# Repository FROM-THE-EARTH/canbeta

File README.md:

# canbeta

東北大学 [FTE](https://www.fte-tohoku.org/) CanSat チーム9期代のプロジェクトです．

## Dependancies

[Pipfile](./Pipfile) を参照してください．
フレームワークは [pisat](https://github.com/jjj999/pisat) を使っています．

## 開発者へ

* 必ずクローンしたら pipenv で Pipfile に沿った仮想環境を作成してください

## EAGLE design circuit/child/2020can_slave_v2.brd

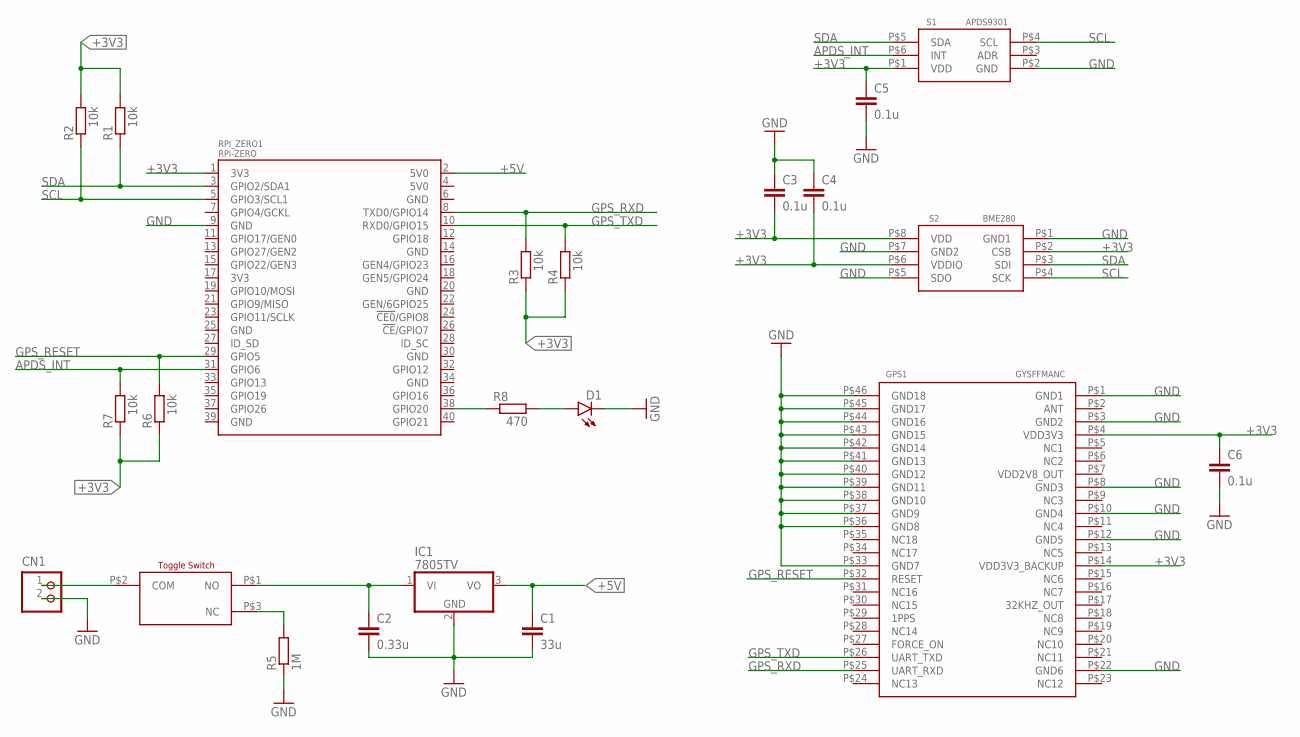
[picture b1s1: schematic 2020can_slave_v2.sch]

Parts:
C1: 33u; C5B3
C2: 0.33u; C5B3
C3, C4, C5, C6: 0.1u; C1206
CN1: B2P-VH
D1: SFH482
GPS1: GYSFFMANC
IC1: 7805TV; TO220V
R1, R2, R3, R4, R6, R7: 10k; R1206
R5: 1M; 0207/10
R8: 470; 0207/10
RPI_ZERO1: RPI-ZERO; RASP_PI_ZERO_BOARD_FULL
S1: APDS9301
S2: BME280
SWITCH_2MS1T2B4M2QES1: SWITCH_2MS1T2B4M2QES

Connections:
+3V3: C3.2, C4.2, C5.1, C6.1, GPS1.P$4 (VDD3V3), GPS1.P$14 (VDD3V3_BACKUP), R1.2, R2.2, R3.1, R4.1, R6.1, R7.1, RPI_ZERO1.1 (3V3), S1.P$1 (VDD), S2.P$2 (CSB), S2.P$6 (VDDIO), S2.P$8 (VDD)
+5V: C1.1, IC1.3 (VO), RPI_ZERO1.2 (5V0)
APDS_INT: R7.2, RPI_ZERO1.31 (GPIO6), S1.P$6 (INT)
GND: C1.2, C2.2, C3.1, C4.1, C5.2, C6.2, CN1.2, D1.K (C), GPS1.P$1 (GND1), GPS1.P$3 (GND2), GPS1.P$8 (GND3), GPS1.P$10 (GND4), GPS1.P$12 (GND5), GPS1.P$22 (GND6), GPS1.P$33 (GND7), GPS1.P$36 (GND8), GPS1.P$37 (GND9), GPS1.P$38 (GND10), GPS1.P$39 (GND11), GPS1.P$40 (GND12), GPS1.P$41 (GND13), GPS1.P$42 (GND14), GPS1.P$43 (GND15), GPS1.P$44 (GND16), GPS1.P$45 (GND17), GPS1.P$46 (GND18), IC1.2 (GND), R5.1, RPI_ZERO1.9 (GND), S1.P$2 (GND), S2.P$1 (GND1), S2.P$5 (SDO), S2.P$7 (GND2)
GPS_RESET: GPS1.P$32 (RESET), R6.2, RPI_ZERO1.29 (GPIO5)
GPS_RXD: GPS1.P$25 (UART_RXD), R3.2, RPI_ZERO1.8 (TXD0/GPIO14)
GPS_TXD: GPS1.P$26 (UART_TXD), R4.2, RPI_ZERO1.10 (RXD0/GPIO15)
unnamed: R8.1, RPI_ZERO1.38 (GPIO20)
unnamed: D1.A, R8.2
unnamed: R5.2, SWITCH_2MS1T2B4M2QES1.P$3 (NC)
SCL: R2.1, RPI_ZERO1.5 (GPIO3/SCL1), S1.P$4 (SCL), S2.P$4 (SCK)
SDA: R1.1, RPI_ZERO1.3 (GPIO2/SDA1), S1.P$5 (SDA), S2.P$3 (SDI)
V+: CN1.1, SWITCH_2MS1T2B4M2QES1.P$2 (COM)
VIN: C2.1, IC1.1 (VI), SWITCH_2MS1T2B4M2QES1.P$1 (NO)

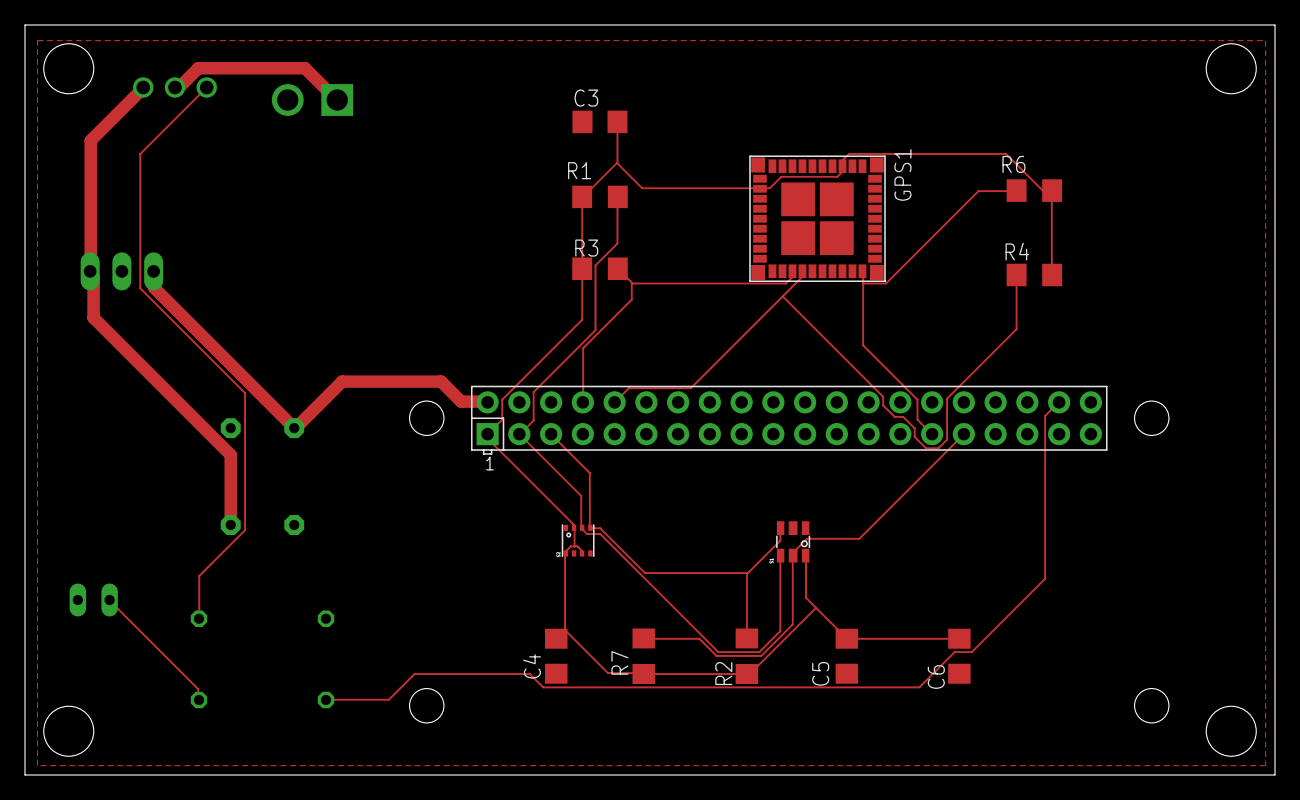
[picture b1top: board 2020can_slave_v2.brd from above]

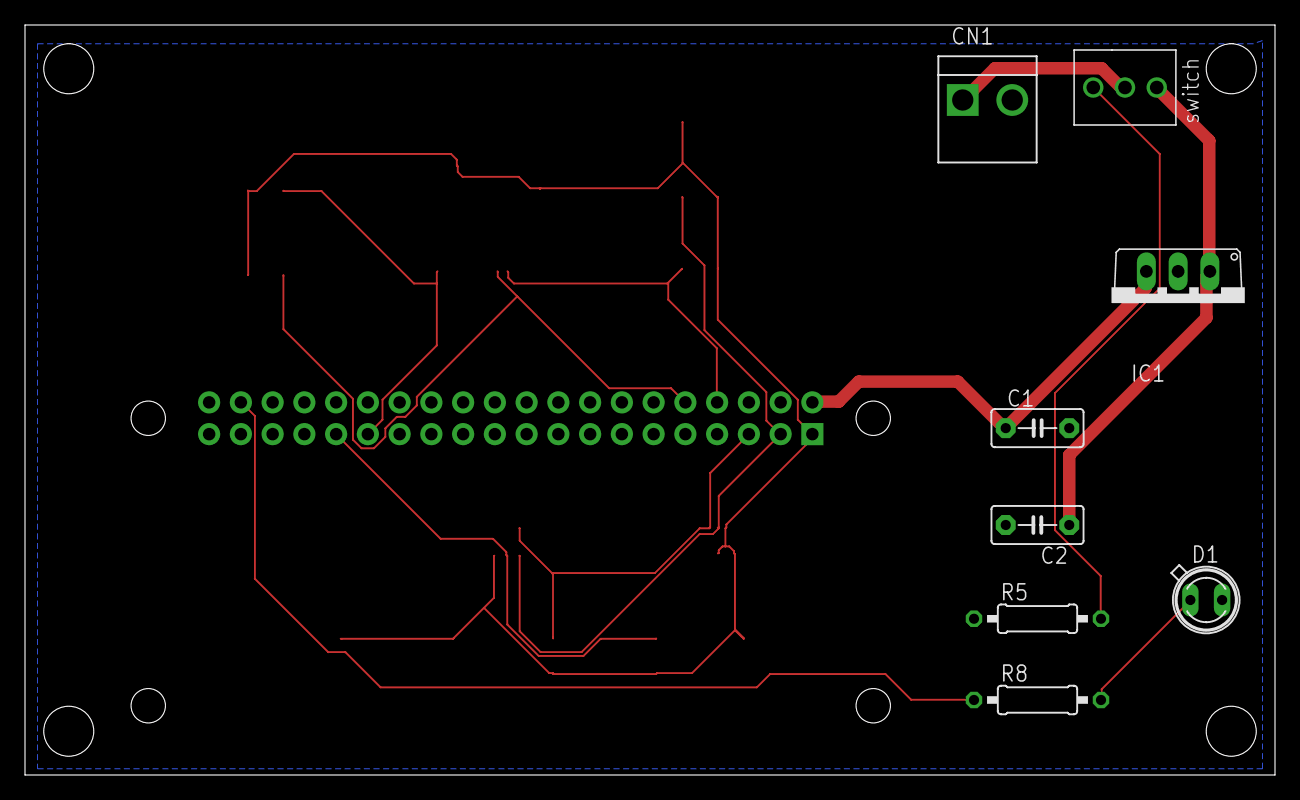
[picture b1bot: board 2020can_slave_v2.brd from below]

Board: 2 copper layers, 100.0 x 60.0 mm, 22 parts (8 on the bottom side), 14 nets.

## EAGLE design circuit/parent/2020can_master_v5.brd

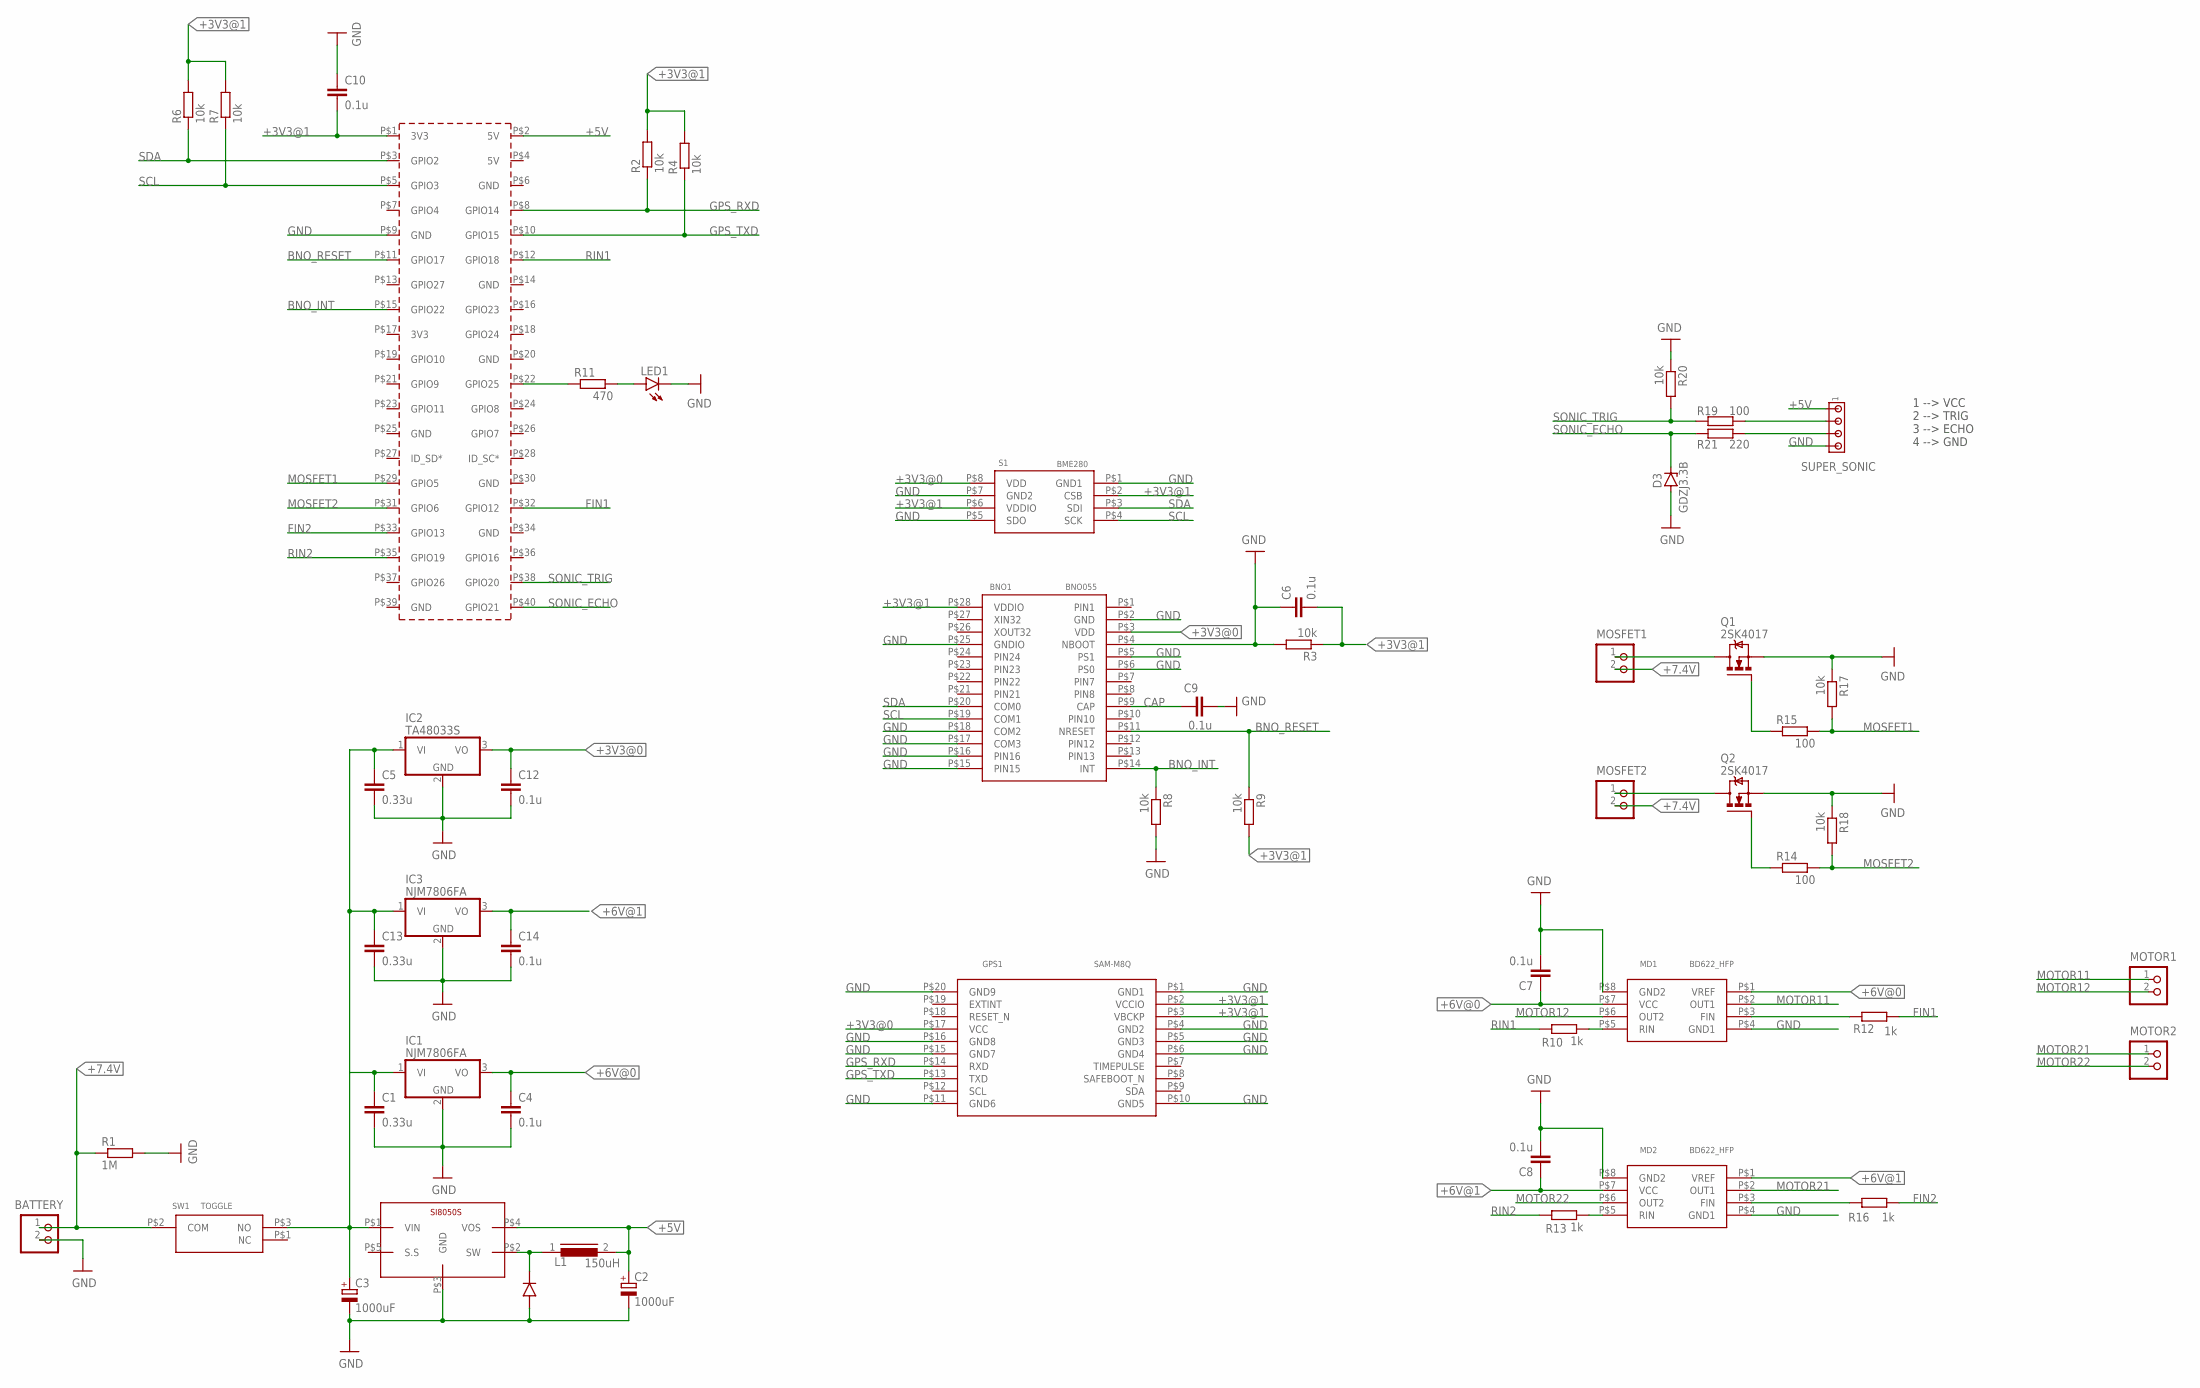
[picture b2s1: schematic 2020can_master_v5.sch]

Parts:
BATTERY: B2P-VH
BNO1: BNO055
C1, C5, C13: 0.33u; C5B3
C2, C3: 1000uF; E5-10,5
C4, C12, C14: 0.1u; C5B3
C6, C7, C8, C9, C10: 0.1u; C1206
D3: GDZJ3.3B; DO35Z10
DIODE_1.1: DIODE_1.5
GPS1: SAM-M8Q
IC1, IC3: NJM7806FA; TO220V
IC2: TA48033S; TO220V
L1: 150uH; SFT830D
LED1: LED5MM
MD1, MD2: BD622_HFP; BD62**_HRP7
MOSFET1, MOSFET2: B2P-VH
MOTOR1, MOTOR2: B2P-VH
PCB1: RPI3RPI3; RPI3
Q1, Q2: 2SK4017; TO220BV
R1: 1M; R2012
R2, R3, R4, R6, R7, R8, R9, R17, R18, R20: 10k; R2012
R10, R12, R13, R16: 1k; R2012
R11: 470; 0207/10
R14, R15, R19: 100; 0207/10
R21: 220; 0207/10
S1: BME280
SI8050S1: SI8050S
SUPER_SONIC: MTA04-100; 10X04MTA
SW1: TOGGLE; TOGGLE_1MS1-T1-B1-M2-Q-N-S

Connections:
+3V3@0: BNO1.P$3 (VDD), C12.1, GPS1.P$17 (VCC), IC2.3 (VO), S1.P$8 (VDD)
+3V3@1: BNO1.P$28 (VDDIO), C6.2, C10.2, GPS1.P$2 (VCCIO), GPS1.P$3 (VBCKP), PCB1.P$1 (3V3), R2.2, R3.1, R4.2, R6.2, R7.2, R9.2, S1.P$2 (CSB), S1.P$6 (VDDIO)
+5V: C2.+, L1.2, PCB1.P$2 (5V), SI8050S1.P$4 (VOS), SUPER_SONIC.1
+6V@0: C4.1, C7.1, IC1.3 (VO), MD1.P$1 (VREF), MD1.P$7 (VCC)
+6V@1: C8.1, C14.1, IC3.3 (VO), MD2.P$1 (VREF), MD2.P$7 (VCC)
+7.4V: BATTERY.1, MOSFET1.2, MOSFET2.2, R1.1, SW1.P$2 (COM)
BNO_INT: BNO1.P$14 (INT), PCB1.P$15 (GPIO22), R8.1
BNO_RESET: BNO1.P$11 (NRESET), PCB1.P$11 (GPIO17), R9.1
CAP: BNO1.P$9 (CAP), C9.1
FIN1: PCB1.P$32 (GPIO12), R12.2
FIN2: PCB1.P$33 (GPIO13), R16.2
GND: BATTERY.2, BNO1.P$2 (GND), BNO1.P$4 (NBOOT), BNO1.P$5 (PS1), BNO1.P$6 (PS0), BNO1.P$15 (PIN15), BNO1.P$16 (PIN16), BNO1.P$17 (COM3), BNO1.P$18 (COM2), BNO1.P$25 (GNDIO), C1.2, C2.-, C3.-, C4.2, C5.2, C6.1, C7.2, C8.2, C9.2, C10.1, C12.2, D3.A, DIODE_1.1.P$1 (ANODE), GPS1.P$1 (GND1), GPS1.P$4 (GND2), GPS1.P$5 (GND3), GPS1.P$6 (GND4), GPS1.P$10 (GND5), GPS1.P$11 (GND6), GPS1.P$15 (GND7), GPS1.P$16 (GND8), GPS1.P$20 (GND9), IC1.2 (GND), IC2.2 (GND), LED1.K (C), MD1.P$4 (GND1), MD1.P$8 (GND2), MD2.P$4 (GND1), MD2.P$8 (GND2), PCB1.P$9 (GND), Q1.S, Q2.S, R1.2, R3.2, R8.2, R17.1, R18.1, R20.1, S1.P$1 (GND1), S1.P$5 (SDO), S1.P$7 (GND2), SI8050S1.P$3 (GND), SUPER_SONIC.4
GPS_RXD: GPS1.P$14 (RXD), PCB1.P$8 (GPIO14), R2.1
GPS_TXD: GPS1.P$13 (TXD), PCB1.P$10 (GPIO15), R4.1
MOSFET1: PCB1.P$29 (GPIO5), R15.2, R17.2
MOSFET2: PCB1.P$31 (GPIO6), R14.2, R18.2
MOTOR11: MD1.P$2 (OUT1), MOTOR1.1
MOTOR12: MD1.P$6 (OUT2), MOTOR1.2
MOTOR21: MD2.P$2 (OUT1), MOTOR2.1
MOTOR22: MD2.P$6 (OUT2), MOTOR2.2
unnamed: DIODE_1.1.P$2 (CATHODE), L1.1, SI8050S1.P$2 (SW)
unnamed: PCB1.P$22 (GPIO25), R11.1
unnamed: C1.1, C3.+, C5.1, C13.1, IC1.1 (VI), IC2.1 (VI), IC3.1 (VI), SI8050S1.P$1 (VIN), SW1.P$3 (NO)
unnamed: LED1.A, R11.2
unnamed: MOSFET1.1, Q1.D
unnamed: MD1.P$3 (FIN), R12.1
unnamed: MOSFET2.1, Q2.D
unnamed: MD1.P$5 (RIN), R10.2
unnamed: Q1.G, R15.1
unnamed: Q2.G, R14.1
unnamed: MD2.P$3 (FIN), R16.1
unnamed: C13.2, C14.2, IC3.2 (GND)
unnamed: MD2.P$5 (RIN), R13.2
unnamed: R19.2, SUPER_SONIC.2
unnamed: R21.2, SUPER_SONIC.3
RIN1: PCB1.P$12 (GPIO18), R10.1
RIN2: PCB1.P$35 (GPIO19), R13.1
SCL: BNO1.P$19 (COM1), PCB1.P$5 (GPIO3), R7.1, S1.P$4 (SCK)
SDA: BNO1.P$20 (COM0), PCB1.P$3 (GPIO2), R6.1, S1.P$3 (SDI)
SONIC_ECHO: D3.C, PCB1.P$40 (GPIO21), R21.1
SONIC_TRIG: PCB1.P$38 (GPIO20), R19.1, R20.2

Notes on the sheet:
1 --> VCC 2 --> TRIG 3 --> ECHO 4 --> GND

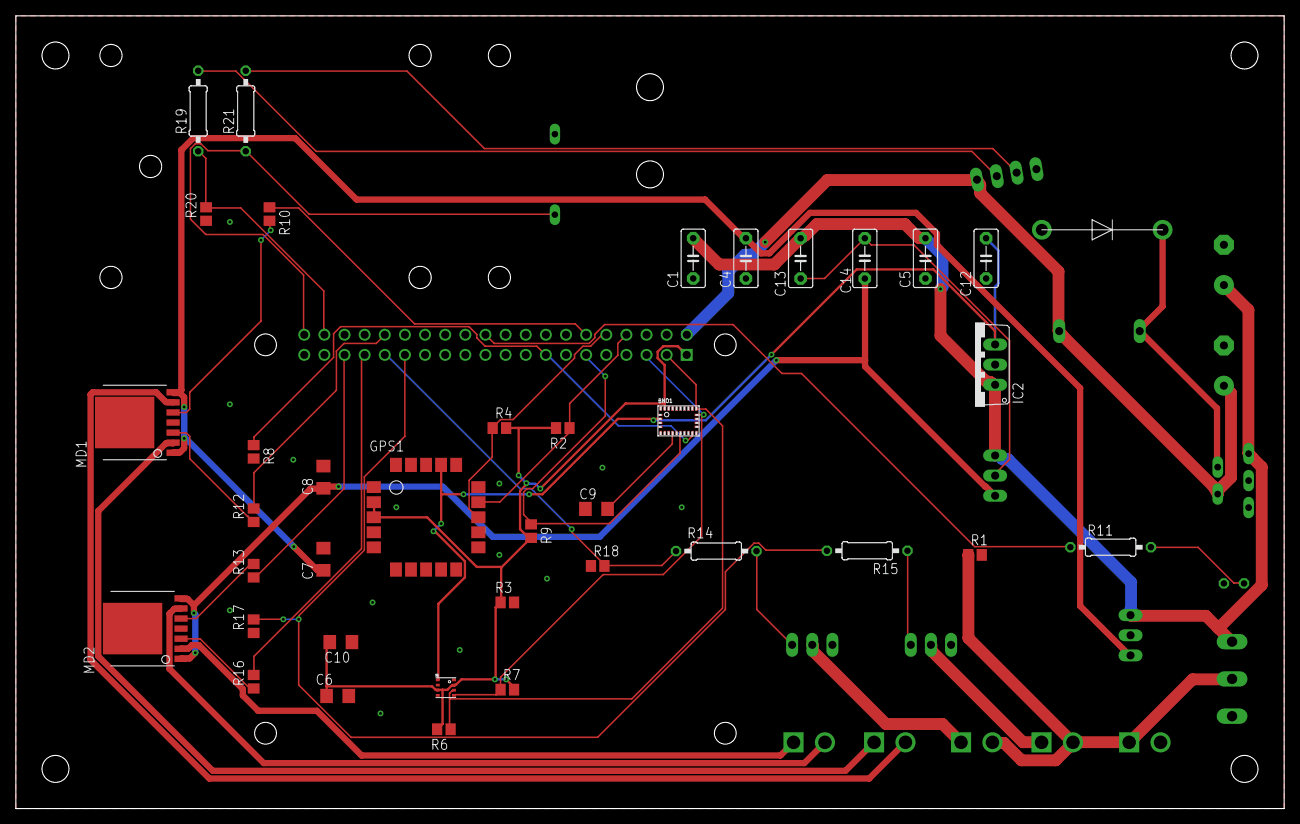
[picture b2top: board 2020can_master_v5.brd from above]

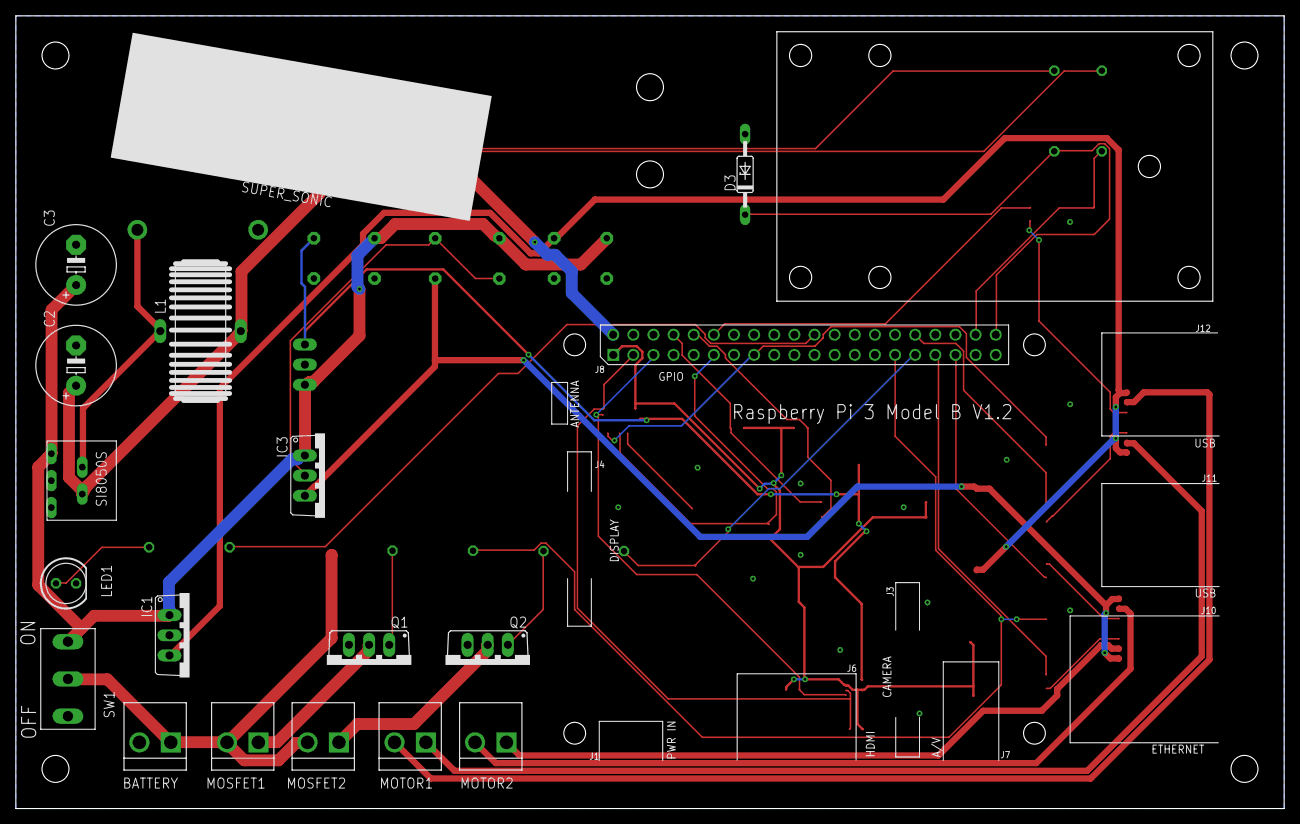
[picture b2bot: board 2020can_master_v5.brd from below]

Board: 2 copper layers, 160.0 x 100.0 mm, 56 parts (18 on the bottom side), 41 nets.

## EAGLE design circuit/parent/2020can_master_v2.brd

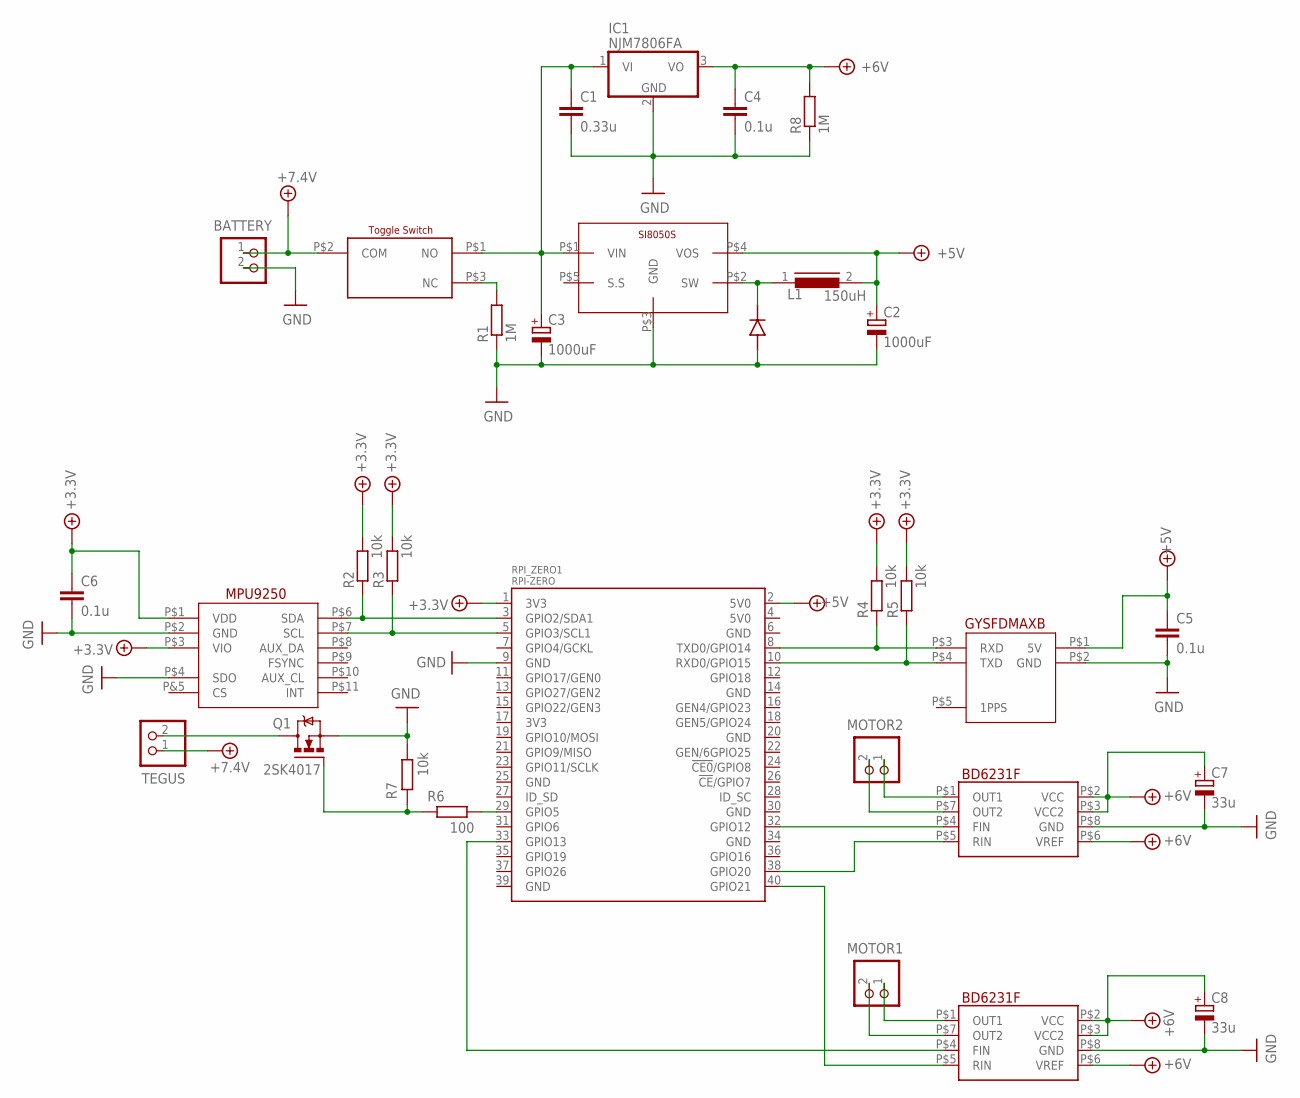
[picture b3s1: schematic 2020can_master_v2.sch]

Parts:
BATTERY: B2P-VH
BD6231F1, BD6231F2: BD6231F; BD62**_SOP8
C1: 0.33u; C5B3
C2, C3: 1000uF; E5-10,5
C4, C5, C6: 0.1u; C5B3
C7, C8: 33u; E2,5-6E
DIODE_1.1: DIODE_1.5
GYSFDMAXB1: GYSFDMAXB
IC1: NJM7806FA; TO220V
L1: 150uH; SFT830D
MOTOR1, MOTOR2: B2P-VH
MPU1: MPU9250
Q1: 2SK4017; TO220BV
R1, R8: 1M; 0207/10
R2, R3, R4, R5, R7: 10k; 0207/10
R6: 100; 0207/10
RPI_ZERO1: RPI-ZERO; RASP_PI_ZERO_BOARD_FULL
SI8050S1: SI8050S
SWITCH_2MS1T2B4M2QES1: SWITCH_2MS1T2B4M2QES
TEGUS: B2P-VH

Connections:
+4.1V: MPU1.P$3 (VIO), R2.2, R3.2, R4.2, R5.2, RPI_ZERO1.1 (3V3)
+5V: C2.+, C5.1, GYSFDMAXB1.P$1 (5V), L1.2, RPI_ZERO1.2 (5V0), SI8050S1.P$4 (VOS)
+7V: BD6231F1.P$2 (VCC), BD6231F1.P$3 (VCC2), BD6231F1.P$6 (VREF), BD6231F2.P$2 (VCC), BD6231F2.P$3 (VCC2), BD6231F2.P$6 (VREF), C4.1, C7.+, C8.+, IC1.3 (VO), R8.2
+8V: BATTERY.1, SWITCH_2MS1T2B4M2QES1.P$2 (COM), TEGUS.1
GND: BATTERY.2, BD6231F1.P$8 (GND), BD6231F2.P$8 (GND), C1.2, C2.-, C3.-, C4.2, C5.2, C6.2, C7.-, C8.-, DIODE_1.1.P$1 (ANODE), GYSFDMAXB1.P$2 (GND), IC1.2 (GND), MPU1.P$2 (GND), MPU1.P$4 (SDO), Q1.S, R1.1, R7.1, R8.1, RPI_ZERO1.9 (GND), SI8050S1.P$3 (GND)
MOS_+: Q1.D, TEGUS.2
unnamed: R1.2, SWITCH_2MS1T2B4M2QES1.P$3 (NC)
unnamed: DIODE_1.1.P$2 (CATHODE), L1.1, SI8050S1.P$2 (SW)
unnamed: MPU1.P$6 (SDA), R2.1, RPI_ZERO1.3 (GPIO2/SDA1)
unnamed: C1.1, C3.+, IC1.1 (VI), SI8050S1.P$1 (VIN), SWITCH_2MS1T2B4M2QES1.P$1 (NO)
unnamed: BD6231F1.P$4 (FIN), RPI_ZERO1.32 (GPIO12)
unnamed: MPU1.P$7 (SCL), R3.1, RPI_ZERO1.5 (GPIO3/SCL1)
unnamed: GYSFDMAXB1.P$3 (RXD), R4.1, RPI_ZERO1.8 (TXD0/GPIO14)
unnamed: GYSFDMAXB1.P$4 (TXD), R5.1, RPI_ZERO1.10 (RXD0/GPIO15)
unnamed: BD6231F1.P$1 (OUT1), MOTOR2.1
unnamed: BD6231F2.P$4 (FIN), RPI_ZERO1.33 (GPIO13)
unnamed: BD6231F1.P$7 (OUT2), MOTOR2.2
unnamed: BD6231F1.P$5 (RIN), RPI_ZERO1.38 (GPIO20)
unnamed: BD6231F2.P$1 (OUT1), MOTOR1.1
unnamed: BD6231F2.P$7 (OUT2), MOTOR1.2
unnamed: BD6231F2.P$5 (RIN), RPI_ZERO1.40 (GPIO21)
unnamed: Q1.G, R6.2, R7.2
unnamed: R6.1, RPI_ZERO1.29 (GPIO5)
unnamed: C6.1, MPU1.P$1 (VDD)

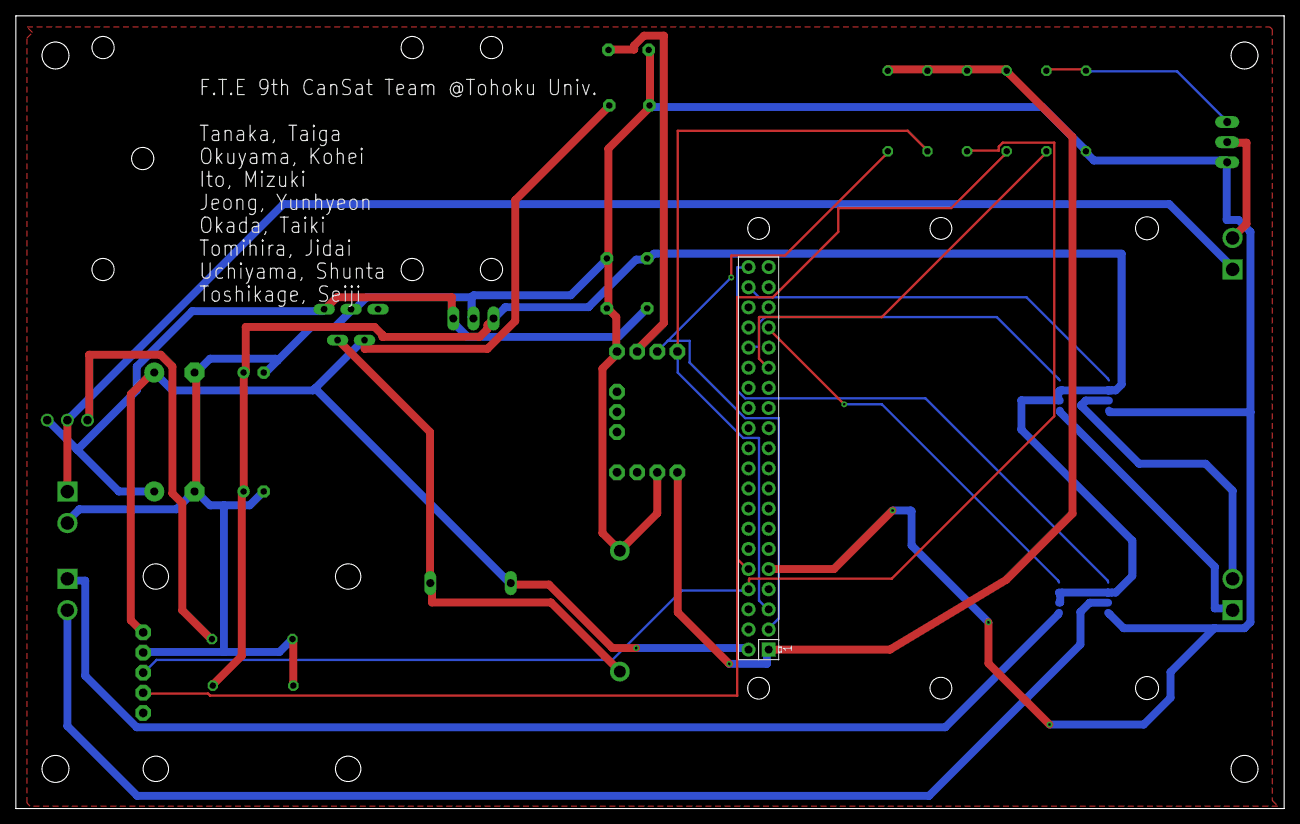
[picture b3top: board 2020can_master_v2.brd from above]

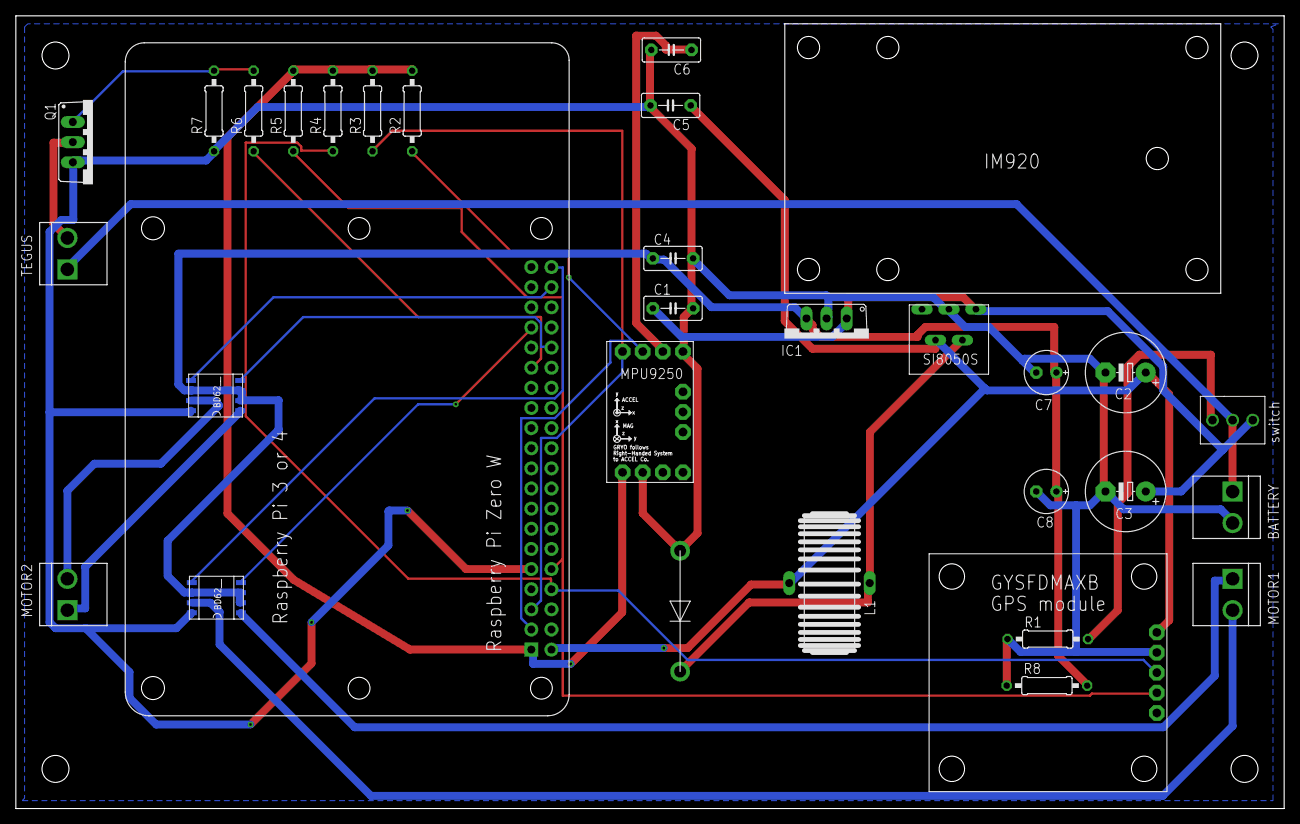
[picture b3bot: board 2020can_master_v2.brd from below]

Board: 2 copper layers, 160.0 x 100.0 mm, 31 parts (30 on the bottom side), 24 nets.

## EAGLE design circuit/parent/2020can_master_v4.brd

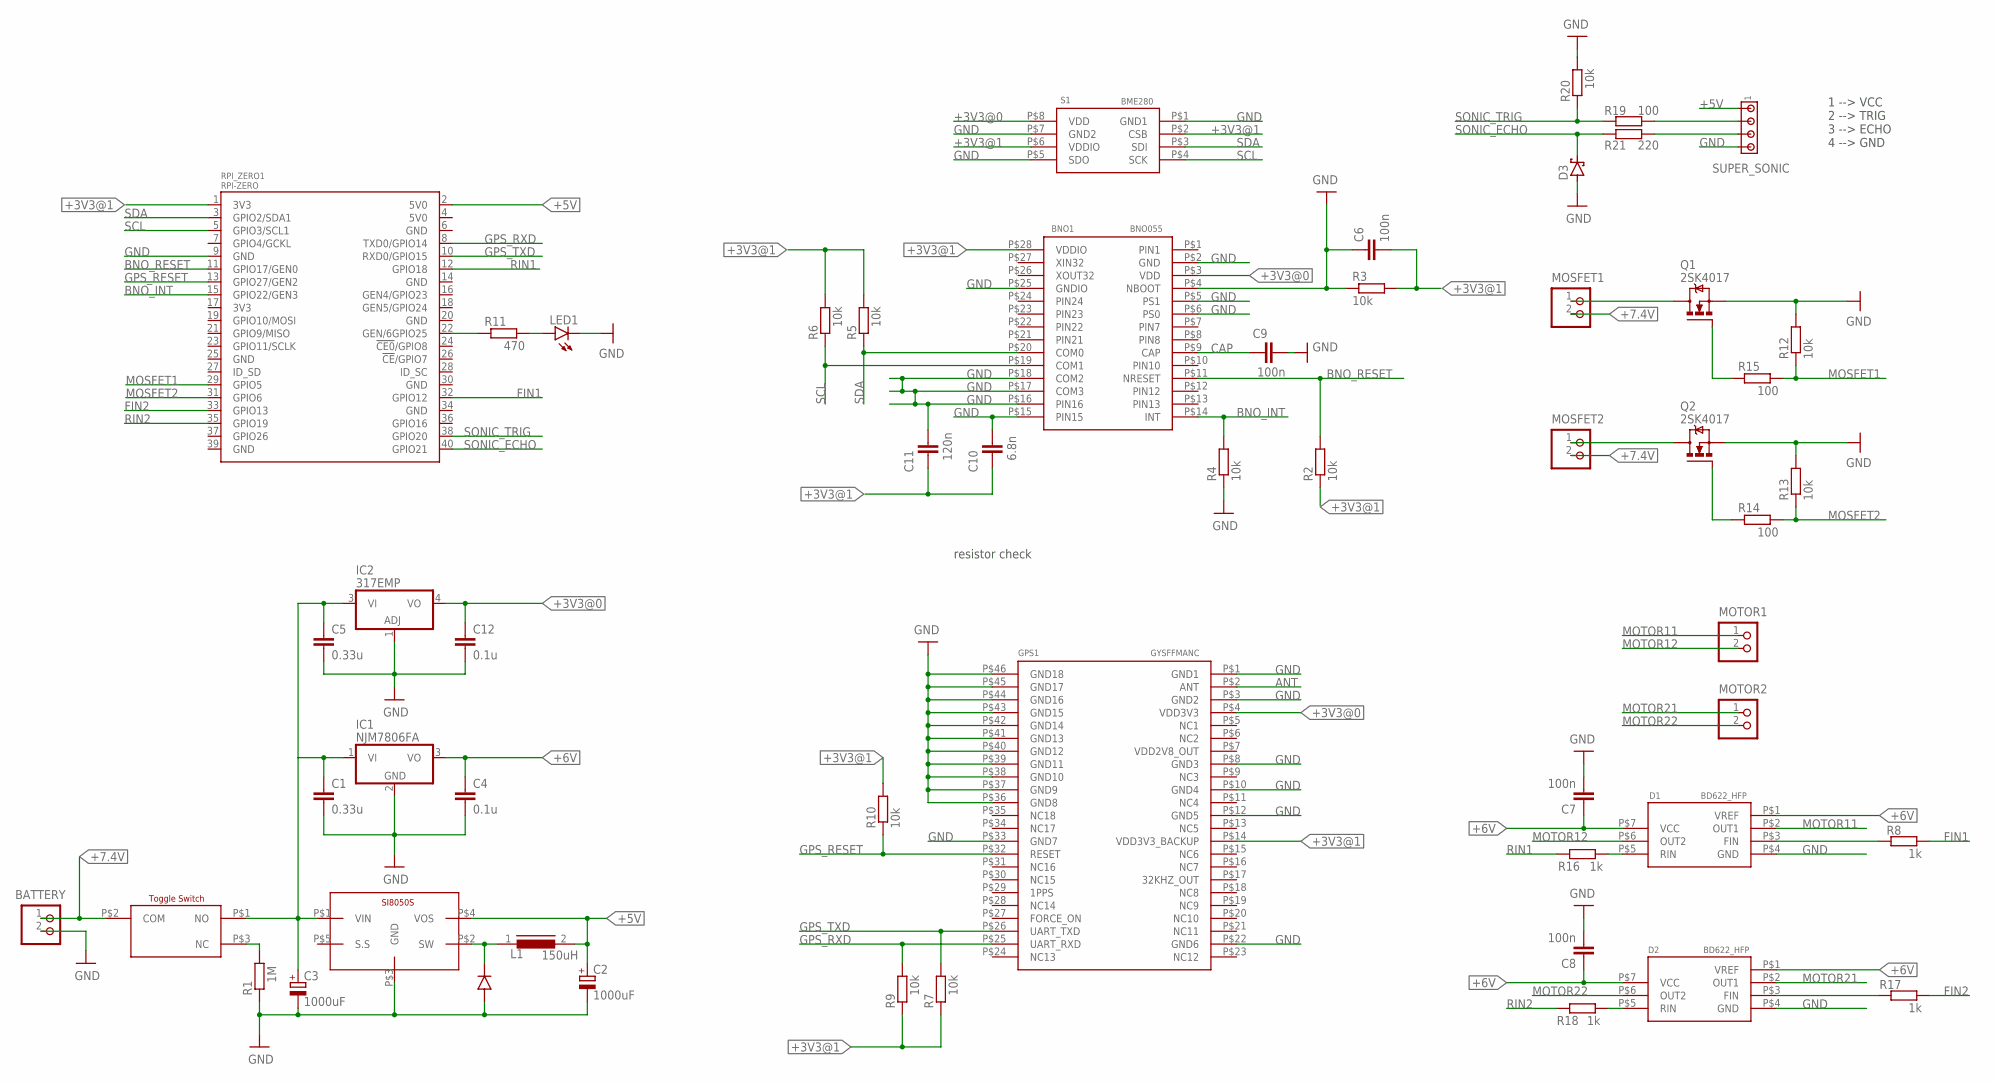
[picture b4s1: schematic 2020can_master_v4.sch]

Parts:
BATTERY: B2P-VH
BNO1: BNO055
C1, C5: 0.33u; C5B3
C2, C3: 1000uF; E5-10,5
C4, C12: 0.1u; C5B3
C6, C7, C8, C9: 100n; C1206
C10: 6.8n; C1206
C11: 120n; C1206
D1, D2: BD622_HFP; BD62**_HRP7
D3: 15KEXXD; DO201T15
DIODE_1.1: DIODE_1.5
GPS1: GYSFFMANC
IC1: NJM7806FA; TO220V
IC2: 317EMP; SOT223
L1: 150uH; SFT830D
LED1: LED5MM
MOSFET1, MOSFET2: B2P-VH
MOTOR1, MOTOR2: B2P-VH
Q1, Q2: 2SK4017; TO220BV
R1: 1M; R1206
R2, R3, R4, R5, R6, R7, R9, R10, R12, R13, R20: 10k; R1206
R8, R16, R17, R18: 1k; R1206
R11: 470; 0207/10
R14, R15, R19: 100; 0207/10
R21: 220; 0207/10
RPI_ZERO1: RPI-ZERO; RASP_PI_ZERO_BOARD_FULL
S1: BME280
SI8050S1: SI8050S
SUPER_SONIC: MTA04-100; 10X04MTA
SWITCH_2MS1T2B4M2QES1: SWITCH_2MS1T2B4M2QES

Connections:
+3V3@0: BNO1.P$3 (VDD), C12.1, GPS1.P$4 (VDD3V3), IC2.4 (VO), S1.P$8 (VDD)
+3V3@1: BNO1.P$28 (VDDIO), C6.2, C10.1, C11.1, GPS1.P$14 (VDD3V3_BACKUP), R2.1, R3.2, R5.2, R6.2, R7.1, R9.1, R10.2, RPI_ZERO1.1 (3V3), S1.P$2 (CSB), S1.P$6 (VDDIO)
+5V: C2.+, L1.2, RPI_ZERO1.2 (5V0), SI8050S1.P$4 (VOS), SUPER_SONIC.1
+6V: C4.1, C7.1, C8.1, D1.P$1 (VREF), D1.P$7 (VCC), D2.P$1 (VREF), D2.P$7 (VCC), IC1.3 (VO)
+7.4V: BATTERY.1, MOSFET1.2, MOSFET2.2, SWITCH_2MS1T2B4M2QES1.P$2 (COM)
ANT: GPS1.P$2 (ANT)
BNO_INT: BNO1.P$14 (INT), R4.2, RPI_ZERO1.15 (GPIO22/GEN3)
BNO_RESET: BNO1.P$11 (NRESET), R2.2, RPI_ZERO1.11 (GPIO17/GEN0)
CAP: BNO1.P$9 (CAP), C9.1
FIN1: R8.1, RPI_ZERO1.32 (GPIO12)
FIN2: R17.1, RPI_ZERO1.33 (GPIO13)
GND: BATTERY.2, BNO1.P$2 (GND), BNO1.P$4 (NBOOT), BNO1.P$5 (PS1), BNO1.P$6 (PS0), BNO1.P$15 (PIN15), BNO1.P$16 (PIN16), BNO1.P$17 (COM3), BNO1.P$18 (COM2), BNO1.P$25 (GNDIO), C1.2, C2.-, C3.-, C4.2, C5.2, C6.1, C7.2, C8.2, C9.2, C10.2, C11.2, C12.2, D1.P$4 (GND), D2.P$4 (GND), D3.A, DIODE_1.1.P$1 (ANODE), GPS1.P$1 (GND1), GPS1.P$3 (GND2), GPS1.P$8 (GND3), GPS1.P$10 (GND4), GPS1.P$12 (GND5), GPS1.P$22 (GND6), GPS1.P$33 (GND7), GPS1.P$36 (GND8), GPS1.P$37 (GND9), GPS1.P$38 (GND10), GPS1.P$39 (GND11), GPS1.P$40 (GND12), GPS1.P$41 (GND13), GPS1.P$42 (GND14), GPS1.P$43 (GND15), GPS1.P$44 (GND16), GPS1.P$45 (GND17), GPS1.P$46 (GND18), IC1.2 (GND), IC2.1 (ADJ), LED1.K (C), Q1.S, Q2.S, R1.1, R3.1, R4.1, R12.2, R13.2, R20.2, RPI_ZERO1.9 (GND), S1.P$1 (GND1), S1.P$5 (SDO), S1.P$7 (GND2), SI8050S1.P$3 (GND), SUPER_SONIC.4
GPS_RESET: GPS1.P$32 (RESET), R10.1, RPI_ZERO1.13 (GPIO27/GEN2)
GPS_RXD: GPS1.P$25 (UART_RXD), R9.2, RPI_ZERO1.8 (TXD0/GPIO14)
GPS_TXD: GPS1.P$26 (UART_TXD), R7.2, RPI_ZERO1.10 (RXD0/GPIO15)
MOSFET1: R12.1, R15.2, RPI_ZERO1.29 (GPIO5)
MOSFET2: R13.1, R14.2, RPI_ZERO1.31 (GPIO6)
MOTOR11: D1.P$2 (OUT1), MOTOR1.1
MOTOR12: D1.P$6 (OUT2), MOTOR1.2
MOTOR21: D2.P$2 (OUT1), MOTOR2.1
MOTOR22: D2.P$6 (OUT2), MOTOR2.2
unnamed: R1.2, SWITCH_2MS1T2B4M2QES1.P$3 (NC)
unnamed: DIODE_1.1.P$2 (CATHODE), L1.1, SI8050S1.P$2 (SW)
unnamed: R11.1, RPI_ZERO1.22 (GEN/6GPIO25)
unnamed: C1.1, C3.+, C5.1, IC1.1 (VI), IC2.3 (VI), SI8050S1.P$1 (VIN), SWITCH_2MS1T2B4M2QES1.P$1 (NO)
unnamed: LED1.A, R11.2
unnamed: MOSFET1.1, Q1.D
unnamed: D1.P$3 (FIN), R8.2
unnamed: MOSFET2.1, Q2.D
unnamed: D1.P$5 (RIN), R16.1
unnamed: Q1.G, R15.1
unnamed: Q2.G, R14.1
unnamed: D2.P$3 (FIN), R17.2
unnamed: D2.P$5 (RIN), R18.1
unnamed: R19.2, SUPER_SONIC.2
unnamed: R21.2, SUPER_SONIC.3
RIN1: R16.2, RPI_ZERO1.12 (GPIO18)
RIN2: R18.2, RPI_ZERO1.35 (GPIO19)
SCL: BNO1.P$19 (COM1), R6.1, RPI_ZERO1.5 (GPIO3/SCL1), S1.P$4 (SCK)
SDA: BNO1.P$20 (COM0), R5.1, RPI_ZERO1.3 (GPIO2/SDA1), S1.P$3 (SDI)
SONIC_ECHO: D3.C, R21.1, RPI_ZERO1.40 (GPIO21)
SONIC_TRIG: R19.1, R20.1, RPI_ZERO1.38 (GPIO20)

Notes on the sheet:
resistor check
1 --> VCC 2 --> TRIG 3 --> ECHO 4 --> GND

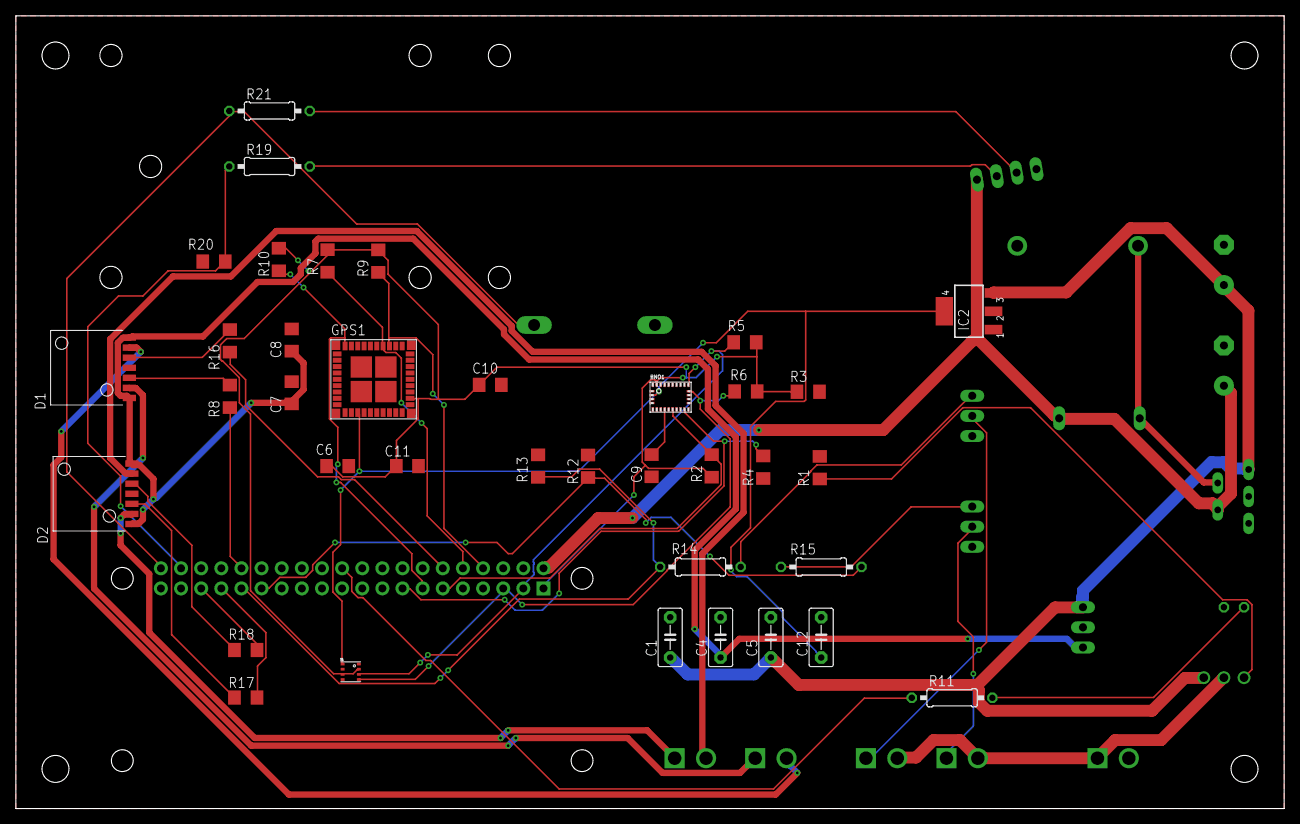
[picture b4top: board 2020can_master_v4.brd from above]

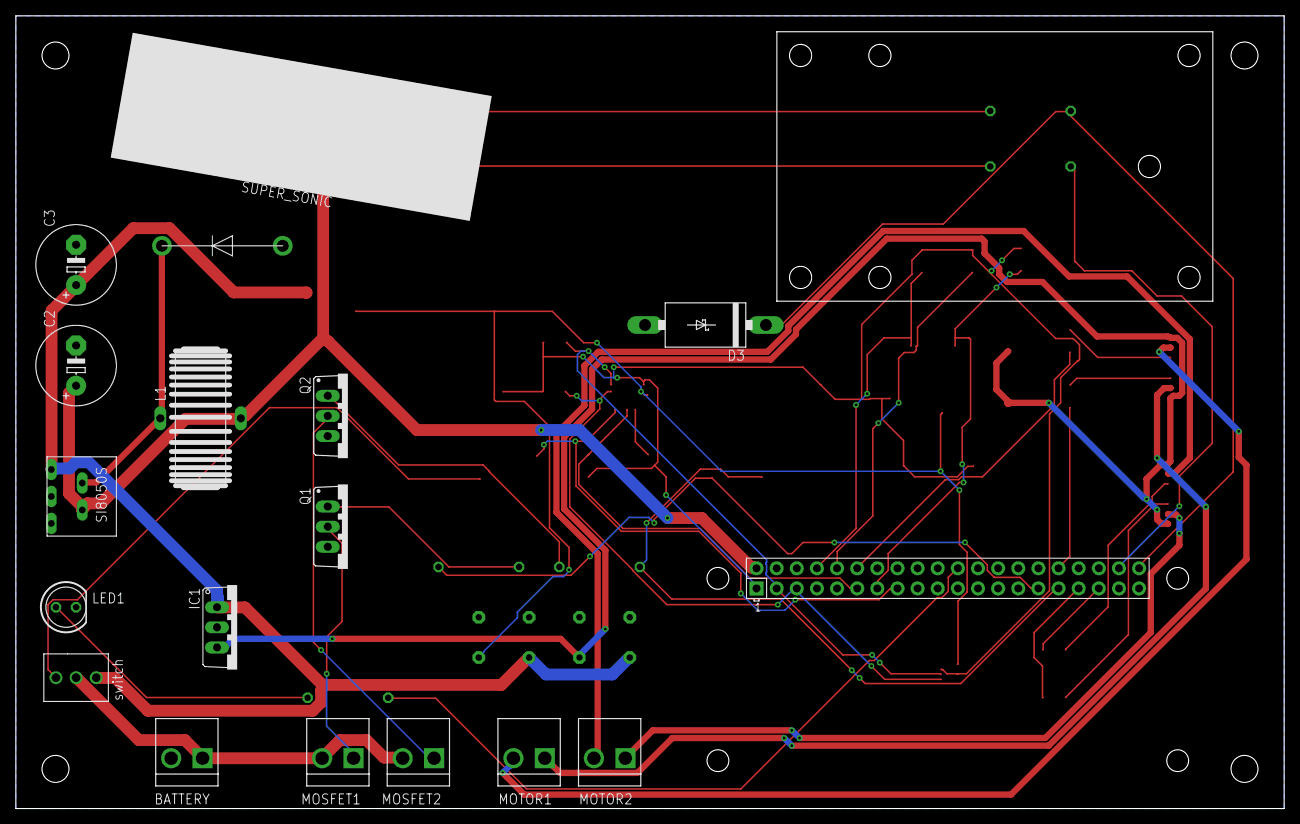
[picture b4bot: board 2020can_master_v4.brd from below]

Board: 2 copper layers, 160.0 x 100.0 mm, 55 parts (18 on the bottom side), 41 nets.
